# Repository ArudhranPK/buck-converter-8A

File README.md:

# buck-converter-8A
## What Is a Buck Converter?
A Buck Converter is a DC-DC converter that steps down the input voltage to a lower output voltage. It is widely used in power electronics for efficient voltage regulation.

## Where Is It Used?
- Consumer Electronics: In devices like smartphones, laptops, and tablets for power management.
- Industrial Systems: For power supplies in manufacturing and automation.
- Renewable Energy Systems: In solar inverters and wind turbines to regulate voltage.
- Automotive Applications: In electric vehicles and hybrid systems for battery management.

## Why Is It Important?
- Efficiency: Buck converters are highly efficient, often reaching over 90% efficiency.
- Compact Design: They are small and lightweight, making them ideal for portable devices.
- Voltage Regulation: They provide stable and precise voltage outputs, crucial for sensitive electronics.

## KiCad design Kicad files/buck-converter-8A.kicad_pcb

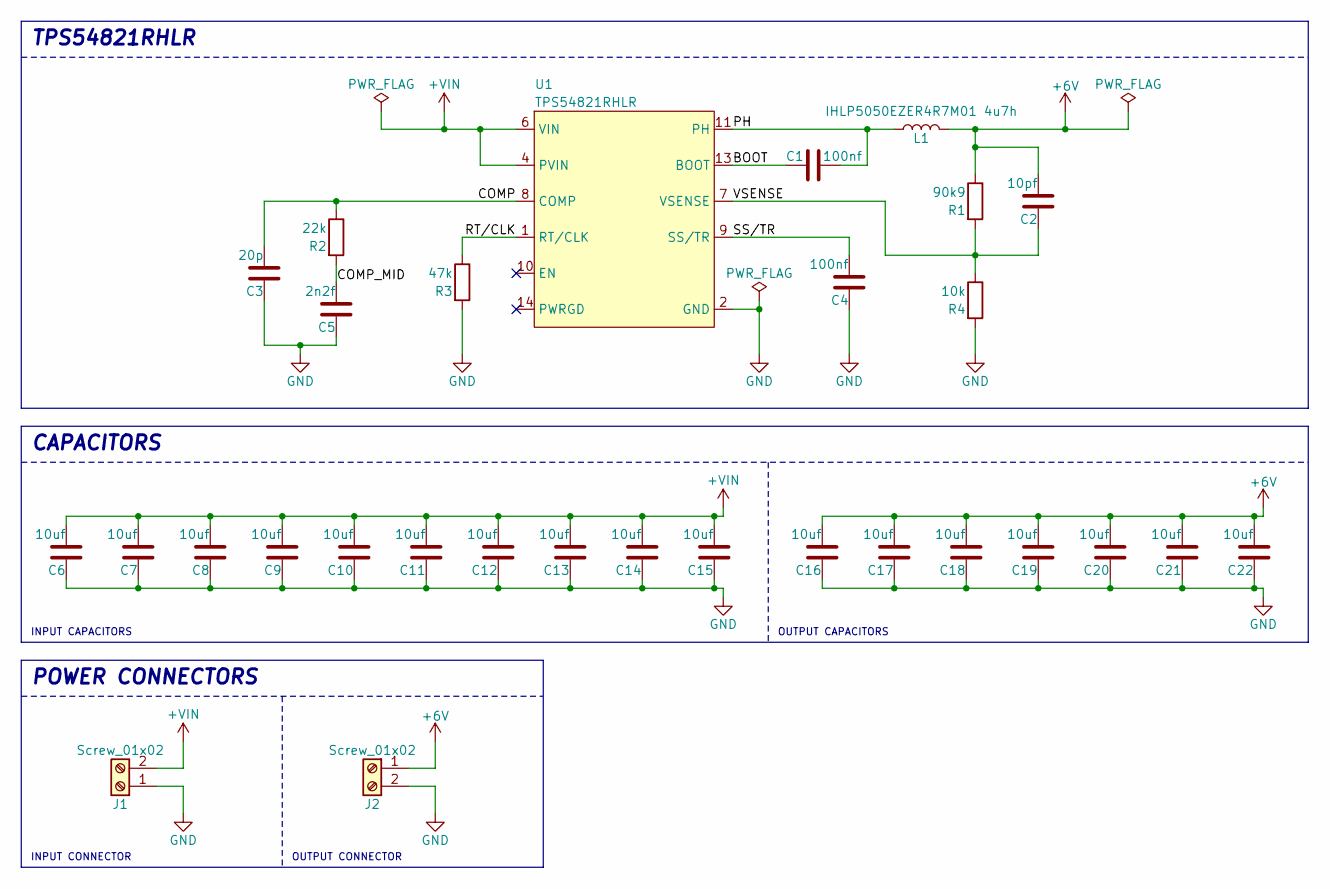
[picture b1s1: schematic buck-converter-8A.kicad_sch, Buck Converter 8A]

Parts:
C1, C4: 100nf; C_0603_1608Metric
C2: 10pf; C_0603_1608Metric
C3: 20p; C_0603_1608Metric
C5: 2n2f; C_0603_1608Metric
C6, C7, C8, C9, C10, C11, C12, C13, C14, C15, C16, C17, C18, C19, C20, C21, C22: 10uf; C_0603_1608Metric
J1, J2: Screw_01x02; TerminalBlock_RND_205-00045_1x02_P5.00mm_Horizontal
L1: IHLP5050EZER4R7M01 4u7h; IHLP5050EZER4R7M01
R1: 90k9; R_0603_1608Metric
R2: 22k; R_0603_1608Metric
R3: 47k; R_0603_1608Metric
R4: 10k; R_0603_1608Metric
U1: TPS54821RHLR

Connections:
+6V: C2.2, C16.2, C17.2, C18.2, C19.2, C20.2, C21.2, C22.2, J2.1, L1.2, R1.1
+VIN: C6.2, C7.2, C8.2, C9.2, C10.2, C11.2, C12.2, C13.2, C14.2, C15.2, J1.2, U1.4 (PVIN), U1.5 (PVIN), U1.6 (VIN)
/BOOT: C1.1, U1.13 (BOOT)
/COMP: C3.2, R2.1, U1.8 (COMP)
/COMP_MID: C5.2, R2.2
/PH: C1.2, L1.1, U1.11 (PH), U1.12 (PH)
/RT/CLK: R3.1, U1.1 (RT/CLK)
/SS/TR: C4.2, U1.9 (SS/TR)
/VSENSE: C2.1, R1.2, R4.1, U1.7 (VSENSE)
GND: C3.1, C4.1, C5.1, C6.1, C7.1, C8.1, C9.1, C10.1, C11.1, C12.1, C13.1, C14.1, C15.1, C16.1, C17.1, C18.1, C19.1, C20.1, C21.1, C22.1, J1.1, J2.2, R3.2, R4.2, U1.2 (GND), U1.3 (GND), U1.15 (THERM_PAD)

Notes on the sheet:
OUTPUT CONNECTOR
OUTPUT CAPACITORS
POWER CONNECTORS
TPS54821RHLR
CAPACITORS
INPUT CONNECTOR
INPUT CAPACITORS

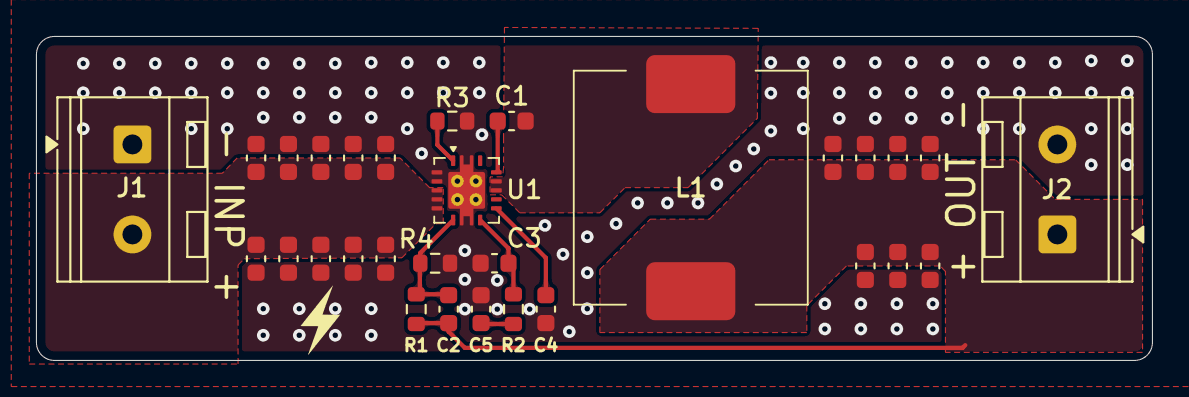
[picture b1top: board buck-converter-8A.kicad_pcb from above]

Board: 2 copper layers, 62.0 x 18.0 mm, 30 parts (0 on the bottom side), 10 nets.

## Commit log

2025-09-13 confirm
2025-09-15 symbol added
2025-09-15 small updates
2025-09-15 footprint added
2025-09-17 SChematics Started
2025-09-17 full schematics done
2025-09-17 minor changes
2025-09-18 minro tweeks
2025-09-21 pcb is done
2025-11-18 final changes
